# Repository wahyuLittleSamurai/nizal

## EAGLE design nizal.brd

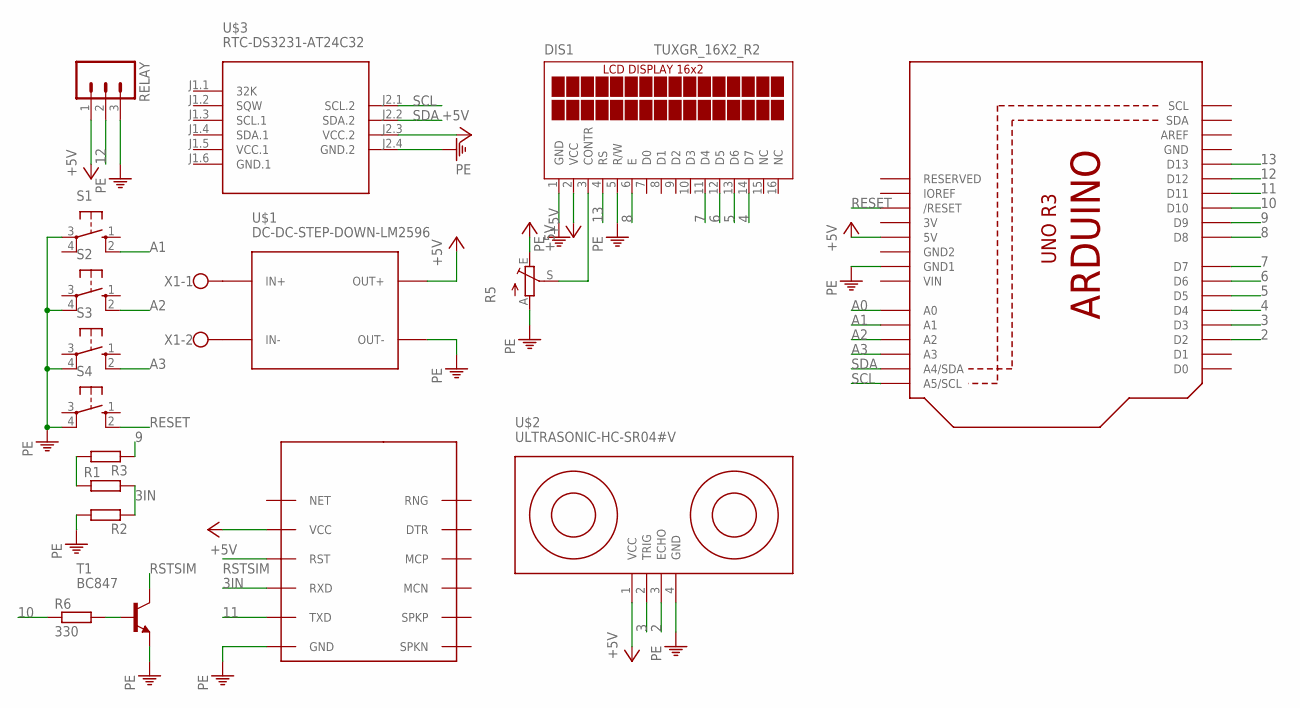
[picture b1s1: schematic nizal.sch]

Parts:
DIS1: TUXGR_16X2_R2
R1, R2, R3: R-EU_M0805; M0805
R5: TRIM_EU-CA6V; CA6V
R6: 330; M0805
RELAY: M03; 03P
S1, S2, S3, S4: 10-XX; B3F-10XX
T1: BC847; SOT23
U1: ARDUINOR3-DIMENSION; ARDUINOR3
U$1: DC-DC-STEP-DOWN-LM2596
U$2: ULTRASONIC-HC-SR04#V
U$3: RTC-DS3231-AT24C32
U$4: SIM800L; SIM-CORE
X1: W237-102

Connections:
2: U1.D2, U$2.3 (ECHO)
3: U1.D3, U$2.2 (TRIG)
3IN: R1.2, R2.1, U$4.RXD
3V: U1.3V
4: DIS1.14 (D7), U1.D4
5: DIS1.13 (D6), U1.D5
6: DIS1.12 (D5), U1.D6
7: DIS1.11 (D4), U1.D7
8: DIS1.6 (E), U1.D8
9: R3.1, U1.D9
10: R6.1, U1.D10
11: U1.D11, U$4.TXD
12: RELAY.2, U1.D12
13: DIS1.4 (RS), U1.D13
+5V: DIS1.2 (VCC), R5.E, RELAY.1, U1.5V, U$1.OUT+, U$2.1 (VCC), U$3.J2.3 (VCC.2), U$4.VCC
A0: U1.A0
A1: S1.2 (S1), U1.A1
A2: S2.2 (S1), U1.A2
A3: S3.2 (S1), U1.A3
GND: U1.GND
GND2: U1.GND2
GND.1: U$3.J1.6 (GND.1)
unnamed: U$1.IN+, X1.1
unnamed: U$1.IN-, X1.2
unnamed: R6.2, T1.1 (B)
unnamed: R1.1, R3.2
unnamed: DIS1.3 (CONTR), R5.S
PE: DIS1.1 (GND), DIS1.5 (R/W), R2.2, R5.A, RELAY.3, S1.3, S2.4 (P1), S3.4 (P1), S4.4 (P1), T1.2 (E), U1.GND1, U$1.OUT-, U$2.4 (GND), U$3.J2.4 (GND.2), U$4.GND
RESET: S4.2 (S1), U1.RESET (/RESET)
RSTSIM: T1.3 (C), U$4.RST
SCL: U1.A5 (A5/SCL), U$3.J2.1 (SCL.2)
SDA: U1.A4 (A4/SDA), U$3.J2.2 (SDA.2)
VCC.1: U$3.J1.5 (VCC.1)
VIN: U1.VIN

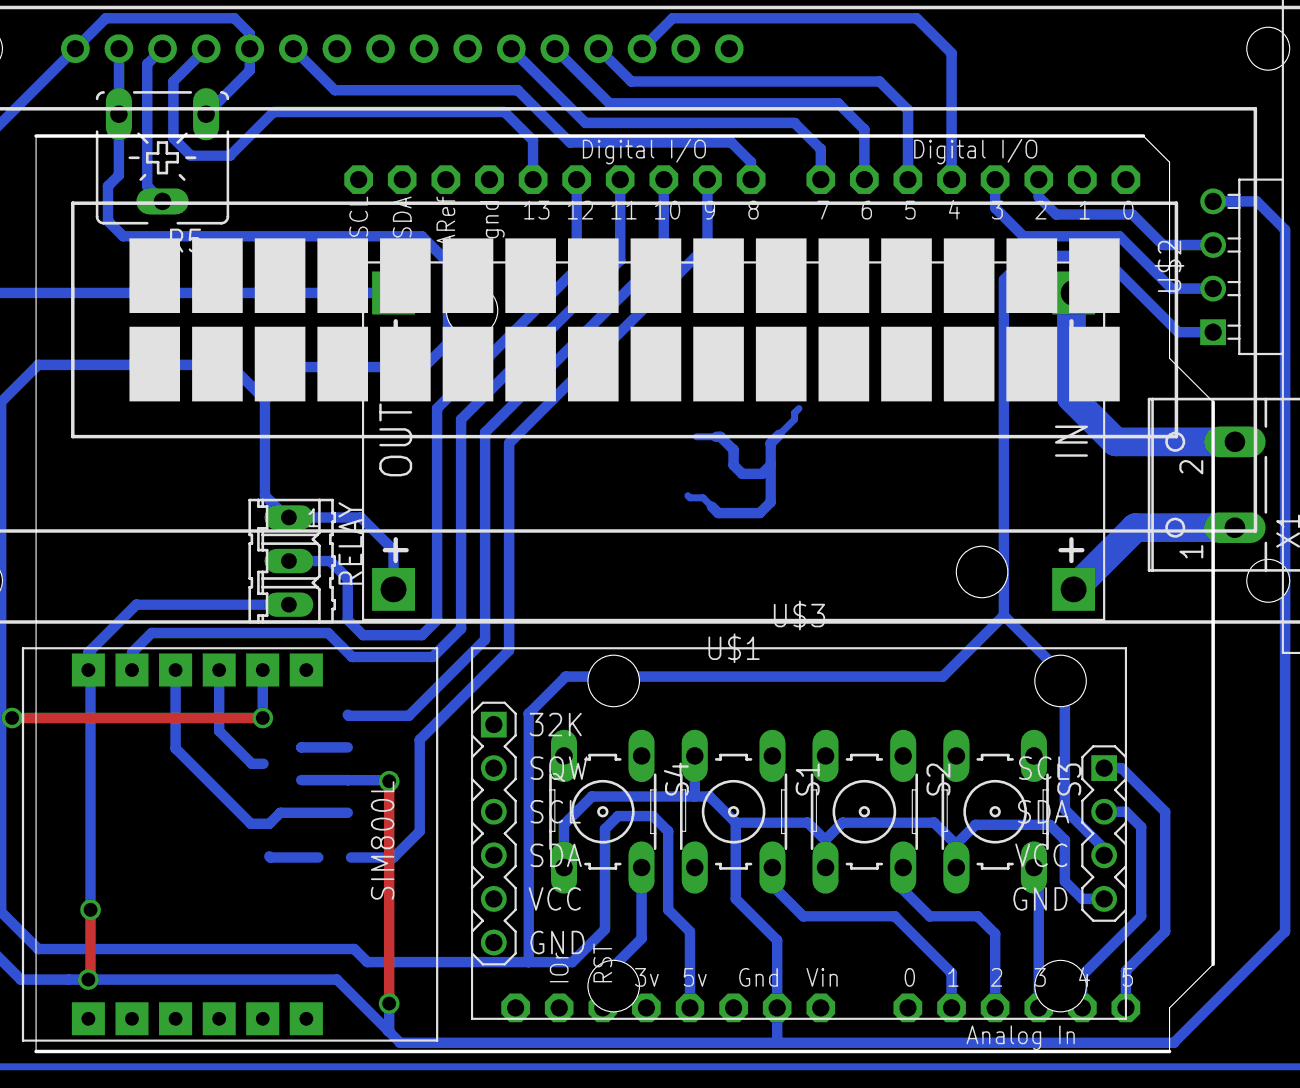
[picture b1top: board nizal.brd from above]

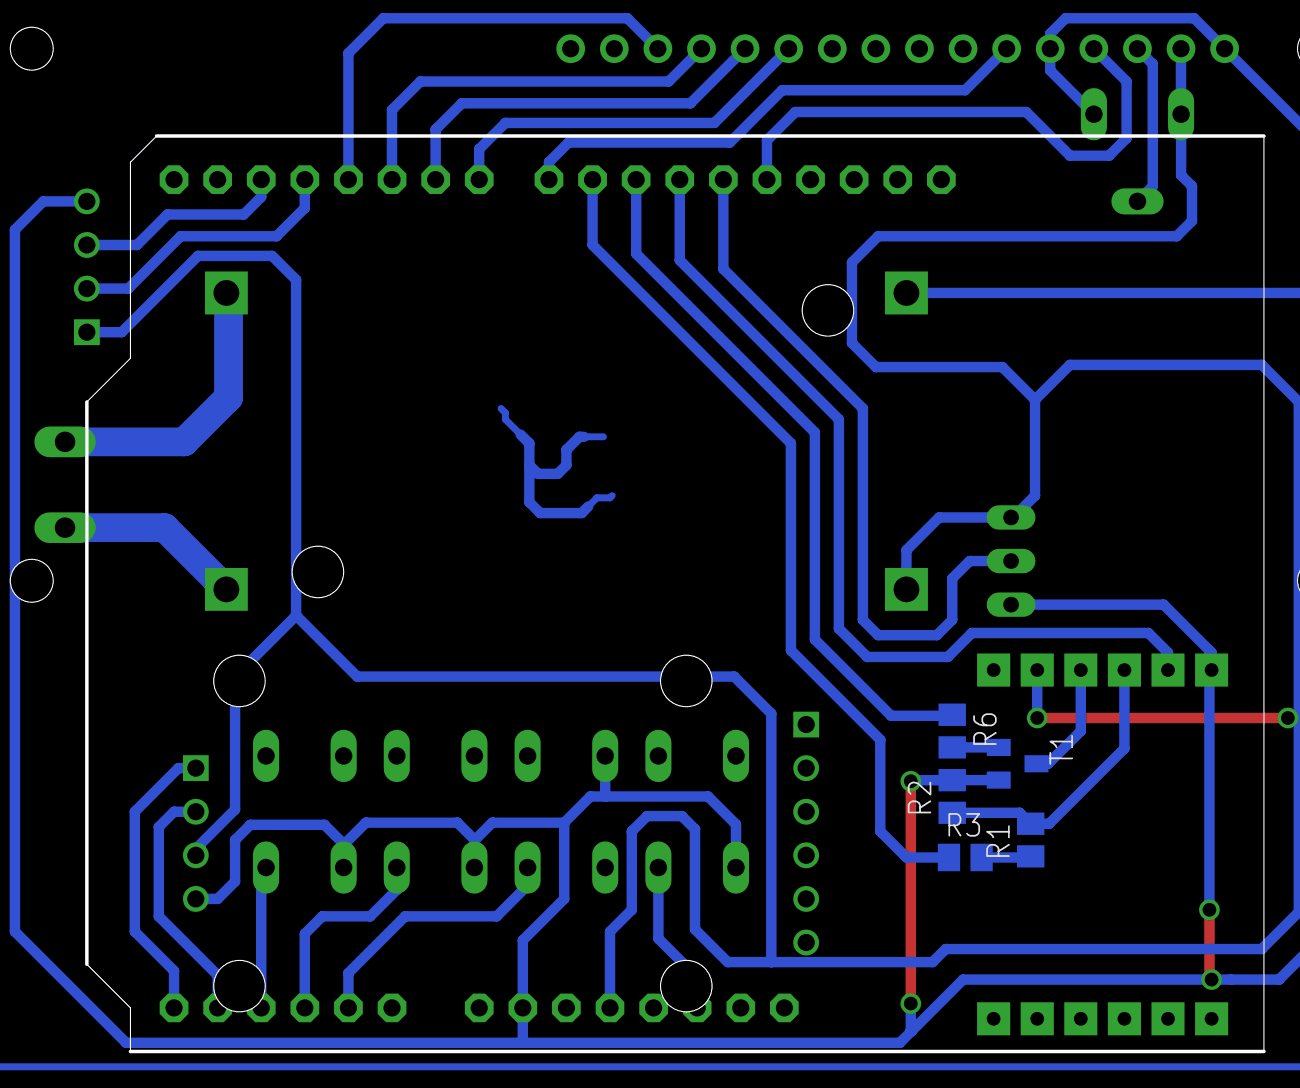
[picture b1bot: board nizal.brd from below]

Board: 2 copper layers, 68.6 x 53.3 mm, 18 parts (5 on the bottom side), 27 nets.

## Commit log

2018-10-15 nizal project

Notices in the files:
parts and their libraries:
zmpt: Released under the Creative Commons Attribution 4.0 International License: http://creativecommons.org/licenses/by/4.0
microbuilder: This work is placed in the public domain, and may be freely used for commercial and non-commercial work with the following conditions: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
